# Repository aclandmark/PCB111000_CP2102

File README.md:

# PCB111000_CP2102

PCB111000 has beeen developed as a learning aid for the C language when applied to AVR devices.  
It consists of a USB bridge to communicate with a PC, an 8 digit display and two AVR devices. 
One of the AVR devices (Atmega 328) hosts a programmer and miniOS which drives the display, 
the other (Atmega168), the user device, hosts user projects.

An I2C bus is used to link the two devices.
All user projects are compiled using Arduino, system projects use Arduino or Studio 7 if needed.
The boards are set up using the UNO to host a bespoke programer.  See repository "UNO_as_an_AVR_programer". 

See repository "PCB-111000/1_Documentation/1_PCB 111000 leaflet.pdf" for general information and a block diagram of the original development. 

There are three versions of PCB111000:

PCB_111000_V2 using two Atmega devices and the FTDI FT230XS USB bridge  
PCB_111000_UNO_V2 A simplified plug in version for use with the UNO  
PCB_111000_CP2102 Using one Atmega one ATtiny and a CP2102 module for USB connectivity.  

In PCB_111000_UNO_V2 and PCB_111000_CP2102 the user device is an Atmega328 which hosts
a bootloader as well as the user projects.

In PCB_111000_CP2102 the I2C bus is replaced with a one wire firmware UART.

PCB111000_CP2102 is assembled using the following steps:

	Prior to assembly a UNO loaded with "UNO_AVR_Programmer" is used to
	program an Atmega328:
	
		With a routine that will be used to calibrate the internal 8MHz clock
		and will then be deleted.
		With a bootloader that will be used for all future programming operations
	
	Post assembly a UPDI programmer is uploaded to the Atmega328 which 
	enables the ATtiny1606 to be programmed with the miniOS.

	Calibration of the ATtiny1606 checked and adjusted if necessary
	
	The pcb is now ready to accept user projects.

	At any stage the UPDI programmer can be rienstated to upgrade the miniOS.

SW used to configure PCB_111000_CP2102  
UNO_AVR_Programmer :	see AVR freaks projects 9 Sept 2020 Slighytly modified  
UNO_UPDI_Programmer: 	Originally writen for the UNO but also runs with an 8MHz clock  
			and can be used here

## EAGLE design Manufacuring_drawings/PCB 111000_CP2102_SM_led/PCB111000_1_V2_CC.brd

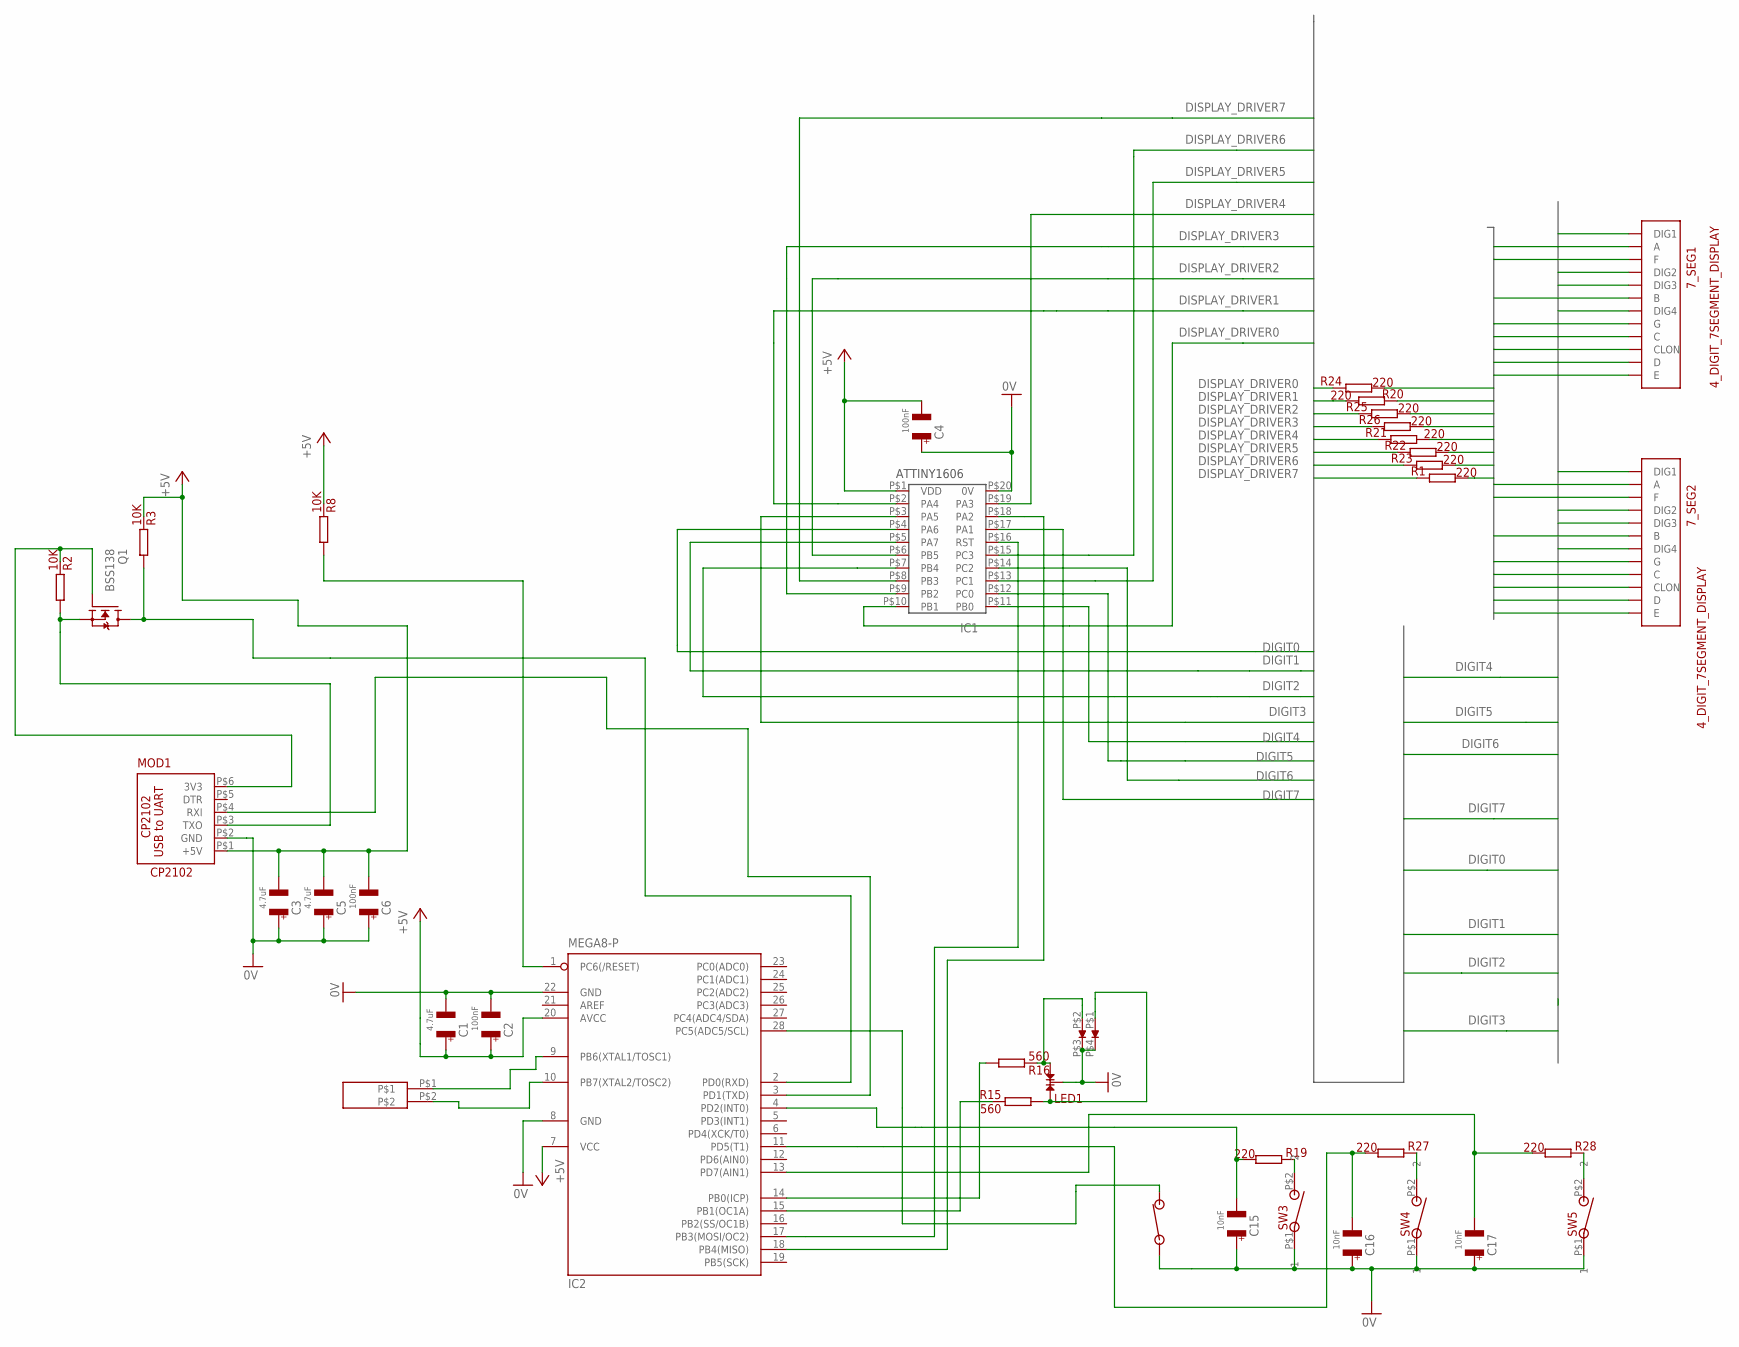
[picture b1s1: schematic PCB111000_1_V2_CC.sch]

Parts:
7_SEG1, 7_SEG2: 4_DIGIT_7SEGMENT_DISPLAY
C1, C3, C5: 4.7uF; 1206@1
C2, C4, C6: 100nF; 1206@1
C15, C16, C17: 10nF; 1206@1
IC1: ATTINY1606
IC2: MEGA8-P; DIL28-3
LED1: LED; CA_DUAL_LED
MOD1: CP2102
Q1: BSS138; SOT23
R1, R19, R20, R21, R22, R23, R24, R25, R26, R27, R28: 220; 1206@1
R2, R3, R8: 10K; 1206@1
R15, R16: 560; 1206@1
SW1: NO_SW; SM_NO_PUSH_BUTTON
SW3, SW4, SW5: NO_PB_1; RE51-0711
U$1: XTAL
U$2: DUAL_SM_LED; SM_DUAL_LED

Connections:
0V: C1.P$2 (2), C2.P$2 (2), C3.P$1 (1), C4.P$1 (1), C5.P$1 (1), C6.P$1 (1), C15.P$1 (1), C16.P$1 (1), C17.P$1 (1), IC1.P$20 (0V), IC2.8 (GND), IC2.22 (GND), LED1.2, MOD1.P$2 (GND), SW1.P$1 (1), SW3.P$1 (1), SW4.P$1 (1), SW5.P$1 (1), U$2.P$3, U$2.P$4
+5V: C1.P$1 (1), C2.P$1 (1), C3.P$2 (2), C4.P$2 (2), C5.P$2 (2), C6.P$2 (2), IC1.P$1 (VDD), IC2.7 (VCC), IC2.20 (AVCC), MOD1.P$1 (+5V), R3.P$2, R8.P$2
DIGIT0: 7_SEG1.P$12 (DIG1), IC1.P$4 (PA6)
DIGIT1: 7_SEG1.P$9 (DIG2), IC1.P$5 (PA7)
DIGIT2: 7_SEG1.P$8 (DIG3), IC1.P$7 (PB4)
DIGIT3: 7_SEG1.P$6 (DIG4), IC1.P$3 (PA5)
DIGIT4: 7_SEG2.P$12 (DIG1), IC1.P$11 (PB0)
DIGIT5: 7_SEG2.P$9 (DIG2), IC1.P$12 (PC0)
DIGIT6: 7_SEG2.P$8 (DIG3), IC1.P$14 (PC2)
DIGIT7: 7_SEG2.P$6 (DIG4), IC1.P$17 (PA1)
DISPLAY_DRIVER0: IC1.P$10 (PB1), R24.P$2
DISPLAY_DRIVER1: IC1.P$2 (PA4), R20.P$1
DISPLAY_DRIVER2: IC1.P$6 (PB5), R25.P$2
DISPLAY_DRIVER3: IC1.P$9 (PB2), R26.P$2
DISPLAY_DRIVER4: IC1.P$19 (PA3), R21.P$2
DISPLAY_DRIVER5: IC1.P$13 (PC1), R22.P$2
DISPLAY_DRIVER6: IC1.P$15 (PC3), R23.P$2
DISPLAY_DRIVER7: IC1.P$8 (PB3), R1.P$2
unnamed: IC2.14 (PB0(ICP)), R16.P$1
unnamed: IC2.15 (PB1(OC1A)), R15.P$2
unnamed: LED1.1, R15.P$1, U$2.P$1
unnamed: LED1.3, R16.P$2, U$2.P$2
unnamed: IC2.28 (PC5(ADC5/SCL)), SW1.P$2 (2)
unnamed: IC1.P$16 (RST), IC2.17 (PB3(MOSI/OC2))
unnamed: R27.P$2, SW4.P$2 (2)
unnamed: R19.P$2, SW3.P$2 (2)
unnamed: C15.P$2 (2), IC2.4 (PD2(INT0)), R19.P$1
unnamed: IC1.P$18 (PA2), IC2.18 (PB4(MISO))
unnamed: C17.P$2 (2), IC2.13 (PD7(AIN1)), R28.P$1
unnamed: IC2.9 (PB6(XTAL1/TOSC1)), U$1.P$1
unnamed: IC2.1 (PC6(/RESET)), R8.P$1
unnamed: IC2.3 (PD1(TXD)), MOD1.P$4 (RXI)
unnamed: MOD1.P$3 (TXO), Q1.2 (S), R2.P$1
unnamed: R28.P$2, SW5.P$2 (2)
unnamed: IC2.10 (PB7(XTAL2/TOSC2)), U$1.P$2
unnamed: MOD1.P$6 (3V3), Q1.1 (G), R2.P$2
unnamed: C16.P$2 (2), IC2.11 (PD5(T1)), R27.P$1
unnamed: IC2.2 (PD0(RXD)), Q1.3 (D), R3.P$1
SEVEN_SEG0: 7_SEG1.P$11 (A), 7_SEG2.P$11 (A), R24.P$1
SEVEN_SEG1: 7_SEG1.P$7 (B), 7_SEG2.P$7 (B), R20.P$2
SEVEN_SEG2: 7_SEG1.P$4 (C), 7_SEG2.P$4 (C), R25.P$1
SEVEN_SEG3: 7_SEG1.P$2 (D), 7_SEG2.P$2 (D), R26.P$1
SEVEN_SEG4: 7_SEG1.P$1 (E), 7_SEG2.P$1 (E), R21.P$1
SEVEN_SEG5: 7_SEG1.P$10 (F), 7_SEG2.P$10 (F), R22.P$1
SEVEN_SEG6: 7_SEG1.P$5 (G), 7_SEG2.P$5 (G), R23.P$1
SEVEN_SEG7: 7_SEG1.P$3 (CLON), 7_SEG2.P$3 (CLON), R1.P$1

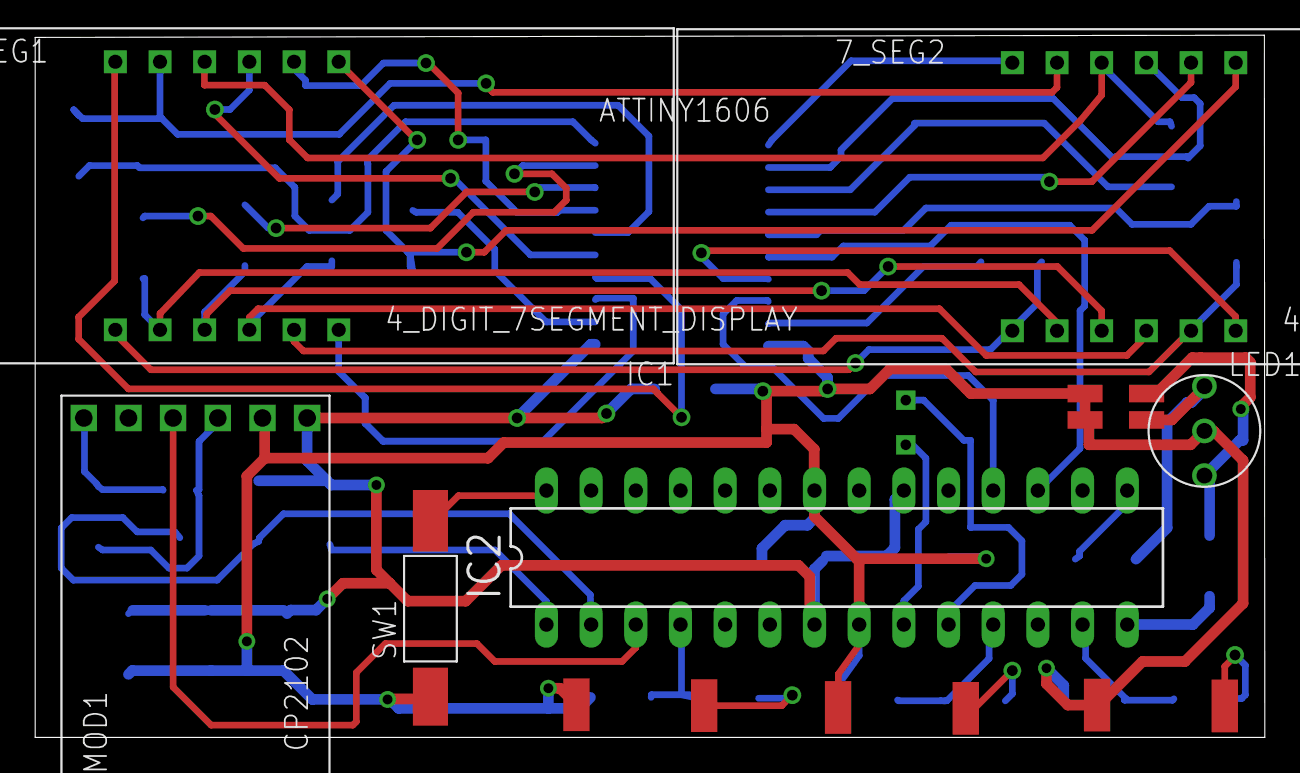
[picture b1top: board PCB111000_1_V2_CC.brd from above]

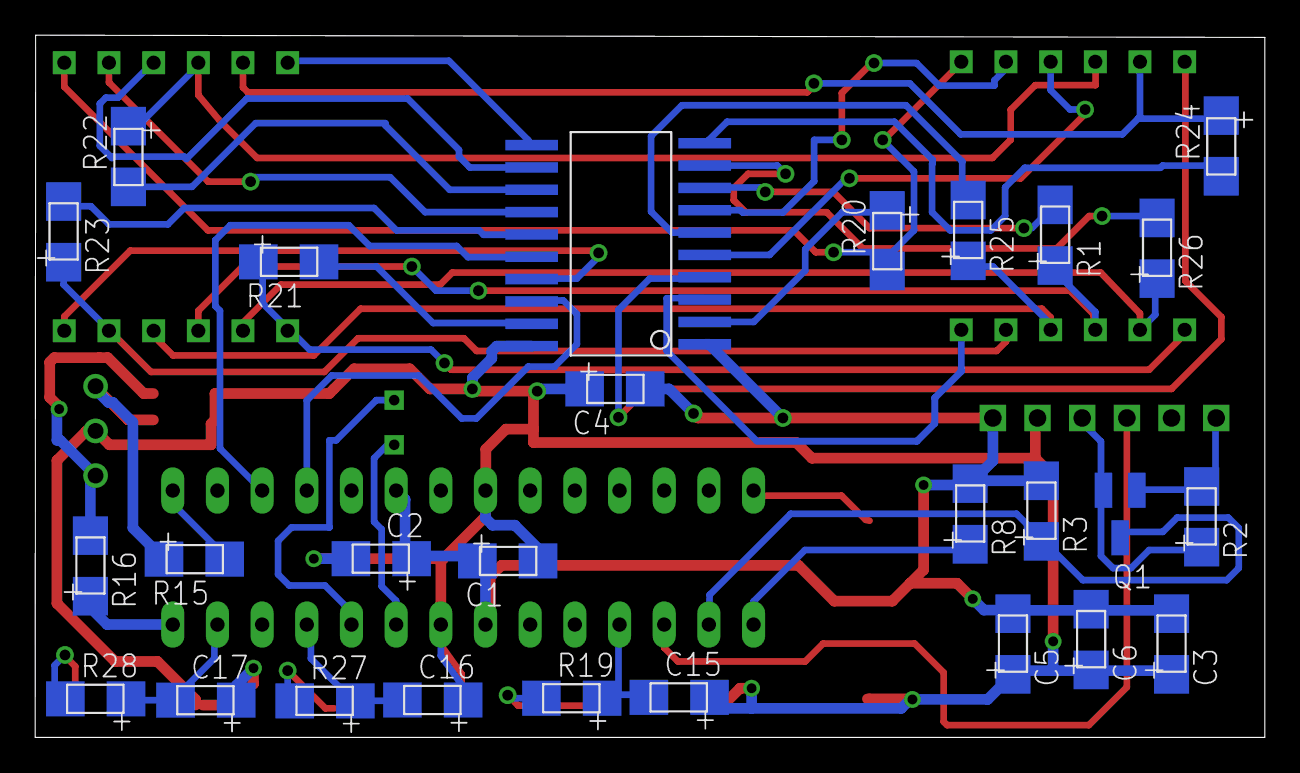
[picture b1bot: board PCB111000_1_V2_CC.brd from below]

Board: 2 copper layers, 69.9 x 39.9 mm, 38 parts (27 on the bottom side), 46 nets.

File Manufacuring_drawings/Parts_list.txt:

Display modules

CA56-12SYKWA	RS 872-1954		Floating point version
CA56-21SYKWA	RS 872-1954		Clock version not available
CC versions not available 08/09/2021


MOD1	From eBay	
1/2/5PCS CP2102 6Pin Serial Converter STC NEW MICRO USB to UART...
Item ID: 185020913574


IC1	ATtiny1606 (SOIC)	Farnell 3018694
IC2	Atmega 328 (DIP)	Farnell 1972087	
28pin IC socket			RS 674-2498

Q1	BSS138	SOT23		RS 671-0324

LED 1	Common cathode RS228-5764

Watch Crystal	RE 90-3044 or 90-3046		RS 547-6985 or 478-9268		 Farnell 2449410

SW1 Surface Mount	RE 51-0709	NO push button (SM)

SW3,4,5	Through hole	RE51-0711	NO push button (with pins)	

R1, R20-26	220R	1206
R19, R27-8	220R	1206

R15, 16		560R	1206

R2, R3, R8	10K	1206

C1, C3, C5 	4.7uF	1206

C2, C4, C6 	100nF	1206

C15-17		10nF	1206

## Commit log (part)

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2022-09-14 Create .~lock.Test_regime.odt#
2022-09-14 Update .~lock.Test_regime.odt#
